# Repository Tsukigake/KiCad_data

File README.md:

# KiCad_data
 
このKiCadデータはロボット部内向けに公開したものでありますので、読みにくいところがあると思いますがご承知おきください。

本リポジトリに掲載されているハードウエア、ソフトウエアおよびシステムに関する情報等の掲載内容は、技術の進歩などにより予告なしに変更されることがあります。

また、上記資料などに記載のデータ、図、表などに示す技術的な内容、プログラム、アルゴリズムその他応用回路例などの情報を使用する場合は、使用者のシステム全体で十分に評価し、使用者の責任において適用可否をご判断ください。

また、このデータを複製、改変しロボットに搭載することによって生じた不具合及び故障についての責任を負いません。

本製品、または本資料に掲載されている技術情報を、大量破壊兵器の開発等の目的、軍事利用の目的、あるいはその他軍事用途の目的で使用しないでください。

ご質問などは https://twitter.com/kamiokannde829 までDMをしていただけたら幸いです。

Kaiyo Academy Robot Club Rescue Department Manager (12th)

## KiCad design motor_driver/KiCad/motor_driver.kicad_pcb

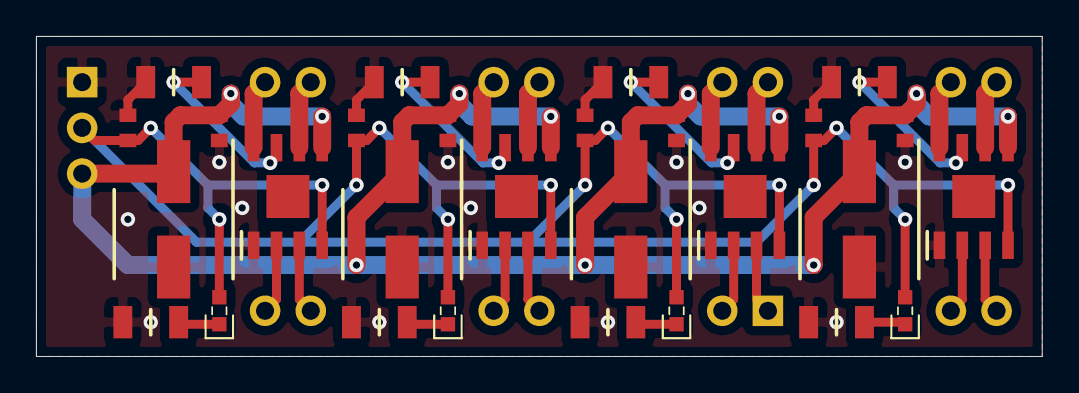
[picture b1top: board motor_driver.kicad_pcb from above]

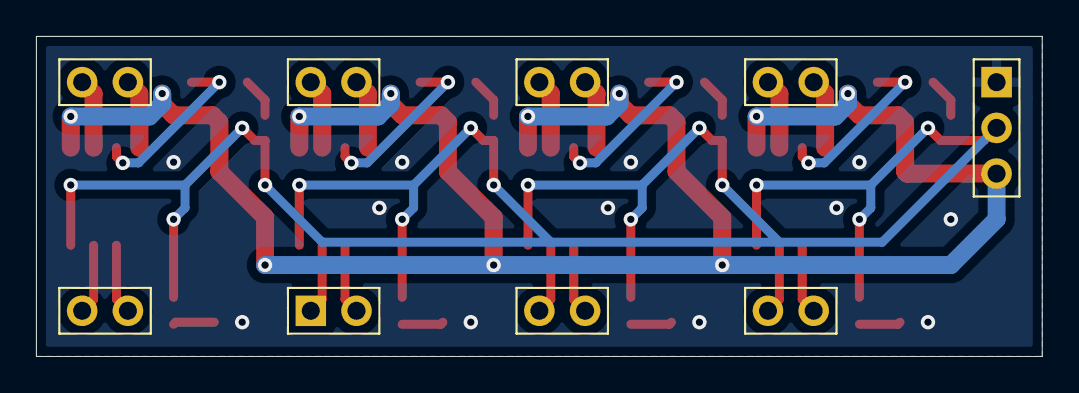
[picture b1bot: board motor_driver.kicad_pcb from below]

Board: 2 copper layers, 55.9 x 17.8 mm, 37 parts (9 on the bottom side), 27 nets.

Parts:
C1, C2, C3, C4, C5, C6, C7, C8: 0.1u; CAPC1608X90N
C9, C10, C11, C12: 47u; CAPAE660X730N
D1, D2, D3, D4: LED; OSXX0603C1E
J1: Conn_01x03_Female; PinHeader_1x03_P2.54mm_Vertical
J2, J3, J4, J5, J6, J7, J8, J9: Conn_01x02_Female; PinHeader_1x02_P2.54mm_Vertical
R1, R2, R3, R4: 110; RESC3216X70N
R5, R6, R7, R8: 1; RESC3216X80N
U3, U4, U5, U6: TB67H450FNG; SOIC127P600X175-9N

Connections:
unnamed: C1.1, C2.1, C3.1, C4.1, D1.2, D2.2, D3.2, D4.2, J1.2, U3.4, U4.4, U5.4, U6.4
unnamed: C1.2, C2.2, C3.2, C4.2, C5.2, C6.2, C7.2, C8.2, C9.2, C10.2, C11.2, C12.2, J1.1, R1.1, R2.1, R3.1, R4.1, R5.1, R6.1, R7.1, R8.1, U3.1, U4.1, U5.1, U6.1
unnamed: C5.1, C6.1, C7.1, C8.1, C9.1, C10.1, C11.1, C12.1, J1.3, U3.5, U4.5, U5.5, U6.5
unnamed: D1.1, R1.2
unnamed: D2.1, R2.2
unnamed: D3.1, R3.2
unnamed: D4.1, R4.2
unnamed: J2.1, U3.3
unnamed: J2.2, U3.2
unnamed: J3.1, U4.3
unnamed: J3.2, U4.2
unnamed: J4.1, U5.3
unnamed: J4.2, U5.2
unnamed: J5.1, U6.3
unnamed: J5.2, U6.2
unnamed: J6.1, U3.8
unnamed: J6.2, U3.6
unnamed: J7.1, U4.8
unnamed: J7.2, U4.6
unnamed: J8.1, U5.8
unnamed: J8.2, U5.6
unnamed: J9.1, U6.8
unnamed: J9.2, U6.6
unnamed: R5.2, U3.7
unnamed: R6.2, U4.7
unnamed: R7.2, U5.7
unnamed: R8.2, U6.7

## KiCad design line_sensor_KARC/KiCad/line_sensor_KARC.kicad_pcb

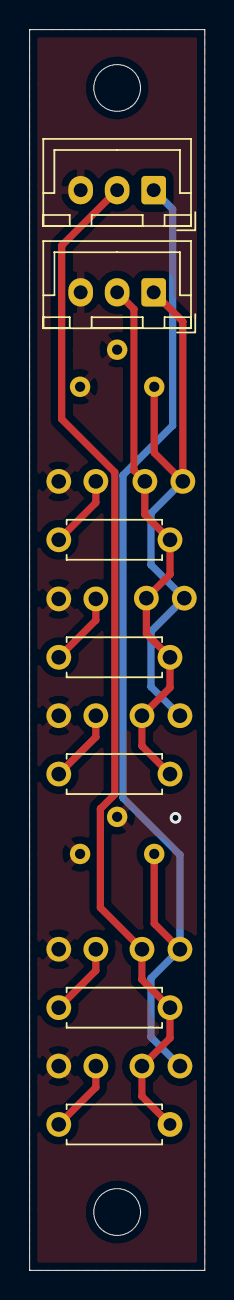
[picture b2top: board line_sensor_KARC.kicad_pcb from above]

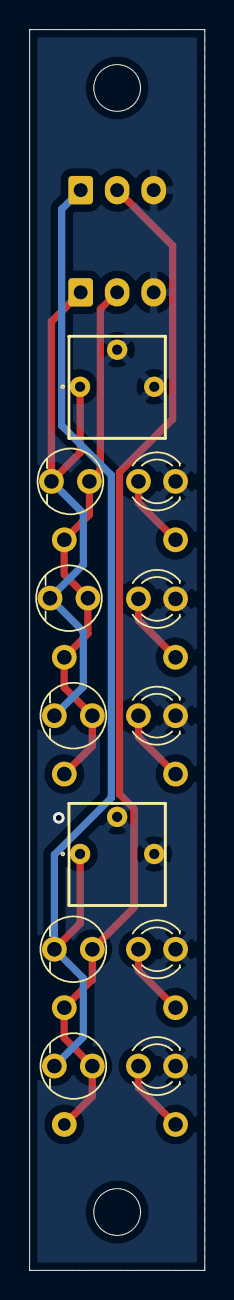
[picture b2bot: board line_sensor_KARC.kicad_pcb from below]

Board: 2 copper layers, 12.0 x 85.0 mm, 19 parts (12 on the bottom side), 10 nets.

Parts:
D1, D2, D3, D4, D5: LED; LED_D3.0mm_Clear
J1, J3: Conn_01x03_Male; JST_XH_B3B-XH-A_1x03_P2.50mm_Vertical
Q1, Q2, Q3, Q4, Q5: Q_Photo_NPN; NJL7502L
R1, R2, R3, R4, R6: R; R_Axial_DIN0207_L6.3mm_D2.5mm_P7.62mm_Horizontal
R5, R7: 3362P-1-203LF; 3362P_1

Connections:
unnamed: D1.1, D2.1, D3.1, D4.1, D5.1, J1.3, J3.3, R5.2, R5.3, R7.2, R7.3
unnamed: D1.2, R1.1
unnamed: D2.2, R2.1
unnamed: D3.2, R3.1
unnamed: D4.2, R4.1
unnamed: D5.2, R6.1
unnamed: J1.1, Q4.2, Q5.2, R5.1
unnamed: J1.2, Q4.1, Q5.1, R4.2, R6.2
unnamed: J3.1, Q1.2, Q2.2, Q3.2, R7.1
unnamed: J3.2, Q1.1, Q2.1, Q3.1, R1.2, R2.2, R3.2
